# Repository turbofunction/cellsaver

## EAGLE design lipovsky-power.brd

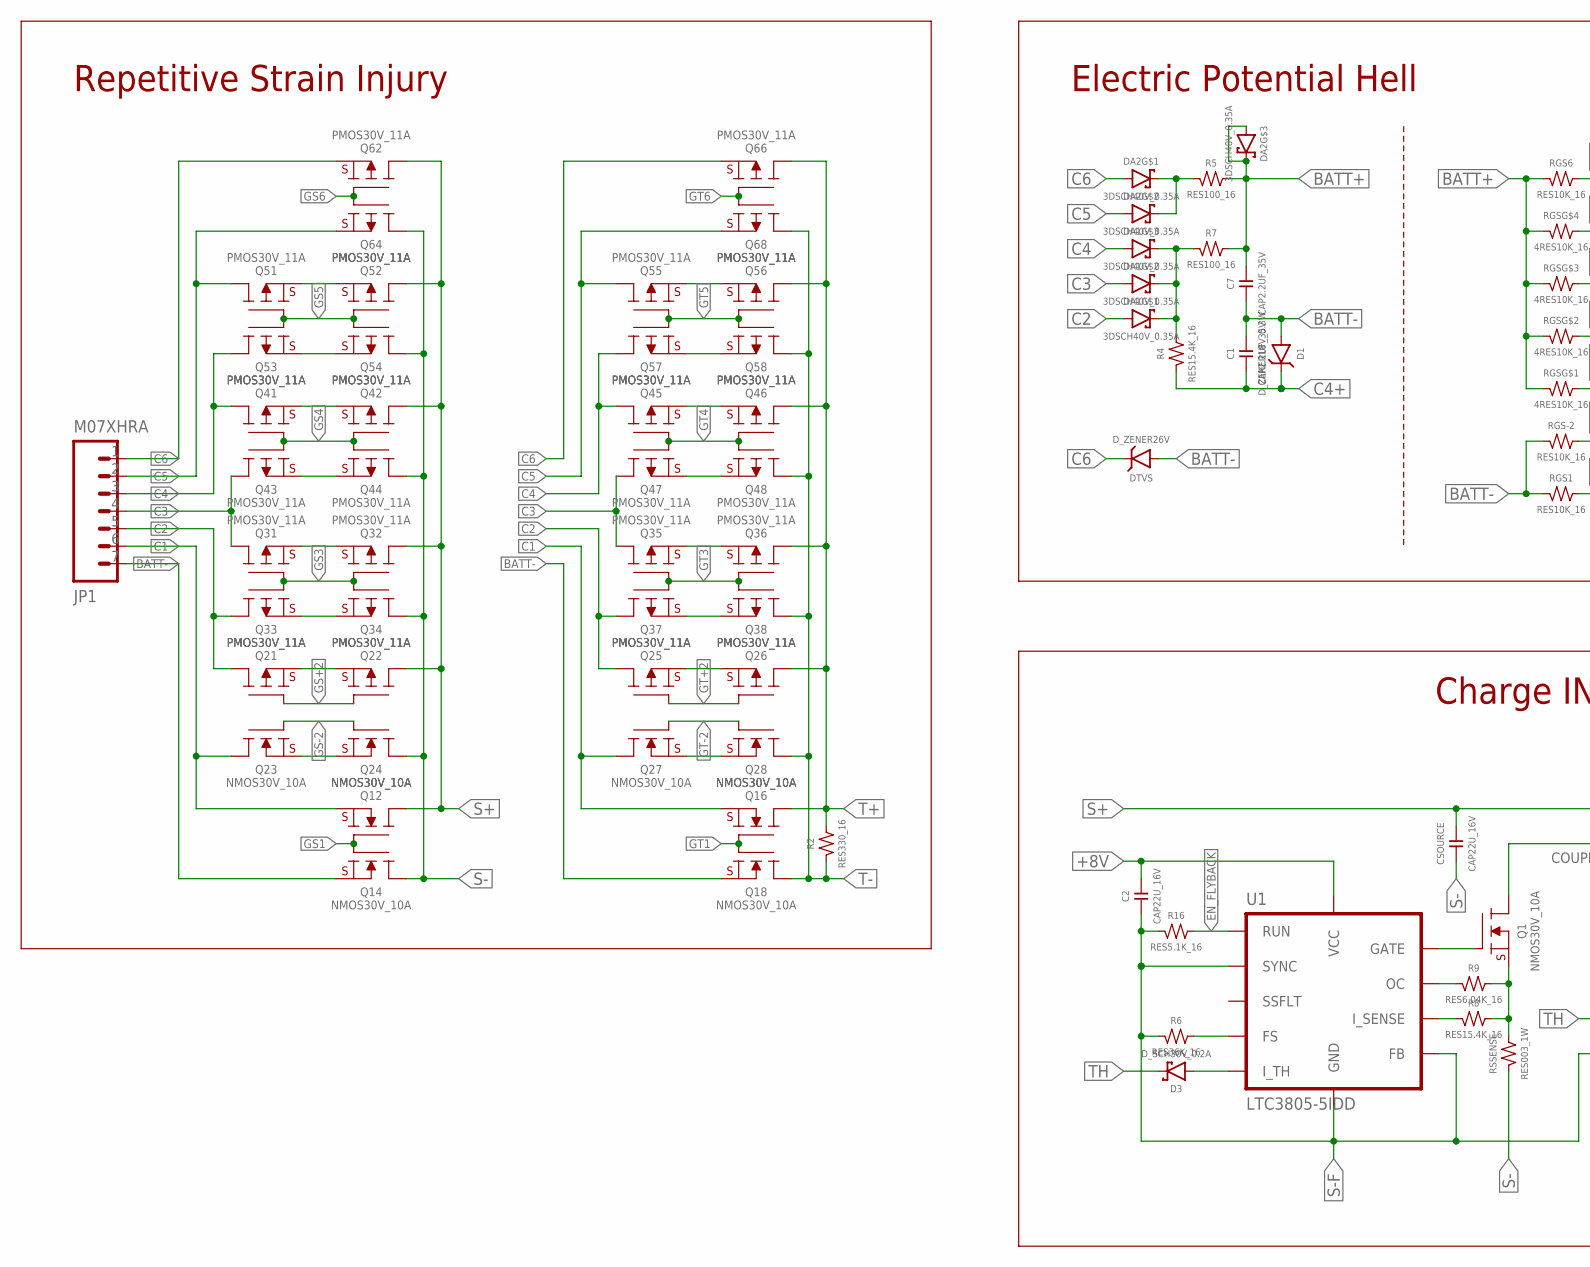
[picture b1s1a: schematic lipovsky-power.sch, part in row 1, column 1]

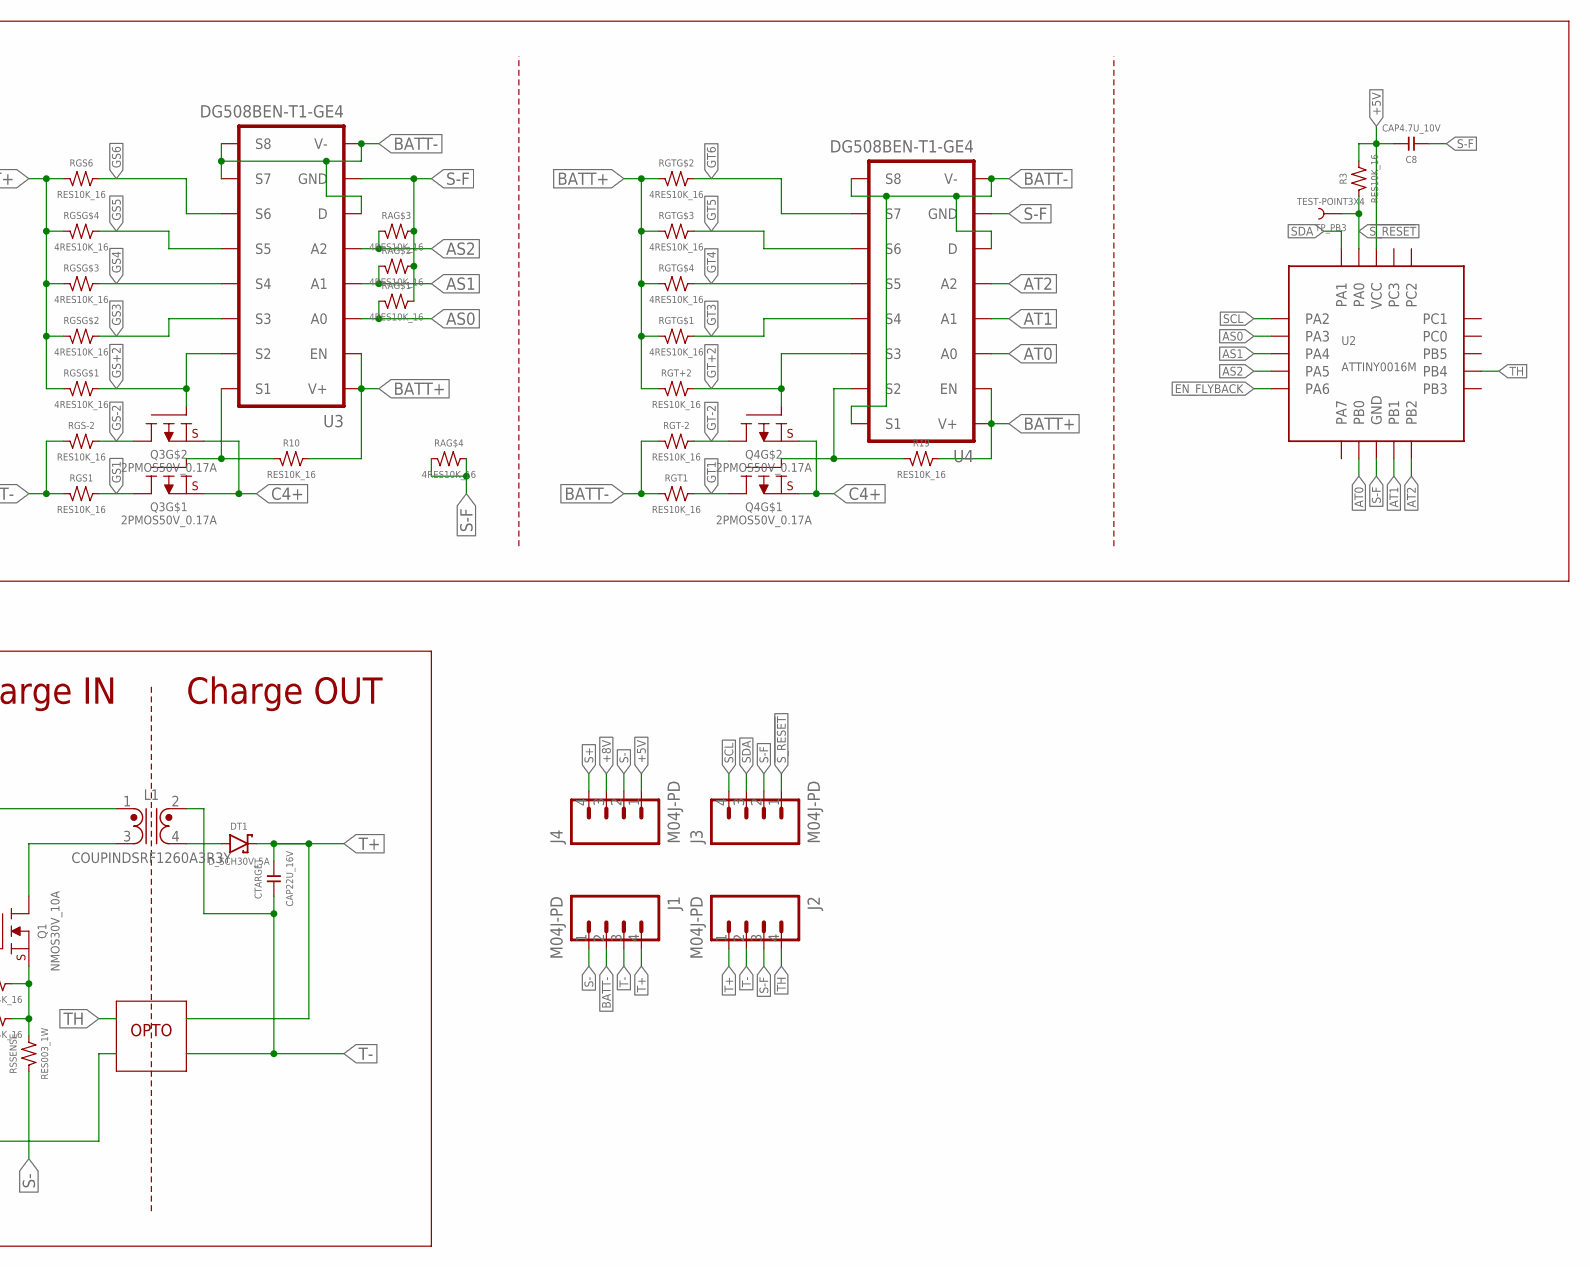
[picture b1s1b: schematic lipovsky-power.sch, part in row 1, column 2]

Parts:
C1, C7: CAP2.2UF_35V; 0402
C2: CAP22U_16V; 0805
C8: CAP4.7U_10V; 0603
CSOURCE: CAP22U_16V; 0805
CTARGET: CAP22U_16V; 0805
D1: D_ZENER18V_0.3W; SOD323+
D3: D_SCH30V_0.2A; SOD523+
DA1, DA2: 3DSCH40V_0.35A; SOT-363
DT1: D_SCH30V_5A; SOD-128
DTVS: D_ZENER26V; 2-UDFN
J1, J2, J3, J4: M04J-PD; 1X04_929J
JP1: M07XHRA; XH07-RA
L1: COUPINDSRF1260A3R3Y; SRF1260A
Q1, Q12, Q14, Q16, Q18, Q23, Q24, Q27, Q28: NMOS30V_10A; 6-POWERWDFN
Q3, Q4: 2PMOS50V_0.17A; SOT-666
Q21, Q22, Q25, Q26, Q31, Q32, Q33, Q34, Q35, Q36, Q37, Q38, Q41, Q42, Q43, Q44, Q45, Q46, Q47, Q48, Q51, Q52, Q53, Q54, Q55, Q56, Q57, Q58, Q62, Q64, Q66, Q68: PMOS30V_11A; 6-POWERWDFN
R2: RES330_16; 0402
R3, R10, R19: RES10K_16; 0402
R4, R8: RES15.4K_16; 0402
R5, R7: RES100_16; 0402
R6: RES36K_16; 0402
R9: RES6.04K_16; 0402
R16: RES5.1K_16; 0402
RA: 4RES10K_16; 1206-QUAD-LS
RGS: 4RES10K_16; 1206-QUAD-LS
RGS1, RGS6: RES10K_16; 0402
RGS-2: RES10K_16; 0402
RGT: 4RES10K_16; 1206-QUAD-LS
RGT1: RES10K_16; 0402
RGT+2: RES10K_16; 0402
RGT-2: RES10K_16; 0402
RSSENSE: RES003_1W; 1206
TP_PB3: TEST-POINT3X4; PAD.03X.04
U1: LTC3805-5IDD; 10-WFDFN
U2: ATTINY0016M; 20-VQFN-2
U3, U4: DG508BEN-T1-GE4; MINIQFN-16L

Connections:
!GS1: Q3.2 (G), R10.1, U3.2 (S1)
!GT1: Q4.2 (G), R19.1, U4.3 (S2)
!S_RESET: J3.1, R3.1, TP_PB3.P$1, U2.19 (PA0)
+5V: C8.2, J4.1, R3.2, U2.4 (VCC)
+8V: C2.2, J4.3, U1.7 (VCC)
AS0: RA.1, U2.2 (PA3), U3.15 (A0)
AS1: RA.2 (1), U2.5 (PA4), U3.14 (A1)
AS2: RA.3 (1), U2.6 (PA5), U3.13 (A2)
AT0: U2.14 (PB0), U4.15 (A0)
AT1: U2.13 (PB1), U4.14 (A1)
AT2: U2.12 (PB2), U4.13 (A2)
BATT+: C7.2, DA2.3 (C), DA2.4 (A), R5.2, R7.2, R10.2, R19.2, RGS.1, RGS.2 (1), RGS.3 (1), RGS.4 (1), RGS6.1, RGT.1, RGT.2 (1), RGT.3 (1), RGT.4 (1), RGT+2.1, U3.11 (V+), U3.16 (EN), U4.11 (V+), U4.16 (EN)
BATT-: C1.2, C7.1, D1.A, DTVS.A, J1.2, JP1.7, Q14.S, Q18.S, RGS1.1, RGS-2.1, RGT1.1, RGT-2.1, U3.1 (V-), U3.6 (D), U3.7 (S8), U3.8 (S7), U4.1 (V-), U4.2 (S1), U4.6 (D), U4.7 (S8)
C1: JP1.6, Q12.S, Q16.S, Q23.D, Q27.D
C2: DA1.6 (A), JP1.5, Q21.D, Q25.D, Q33.D, Q37.D
C3: DA1.5 (A), JP1.4, Q31.D, Q35.D, Q43.D, Q47.D
C4: DA1.4 (A), JP1.3, Q41.D, Q45.D, Q53.D, Q57.D
C4+: C1.1, D1.C, Q3.1 (S), Q3.4 (S), Q4.1 (S), Q4.4 (S), R4.1
C4D: DA1.1 (C), DA1.2 (C), DA1.3 (C), R4.2, R7.1
C5: DA2.5 (A), JP1.2, Q51.D, Q55.D, Q64.S, Q68.S
C6: DA2.6 (A), DTVS.C, JP1.1, Q62.S, Q66.S
C6D: DA2.1 (C), DA2.2 (C), R5.1
EN_FLYBACK: R16.2, U1.4 (RUN), U2.7 (PA6)
FS: R6.2, U1.5 (FS)
GATE: Q1.G, U1.6 (GATE)
GS1: Q3.6 (D), Q12.G, Q14.G, RGS1.2
GS3: Q31.G, Q32.G, Q33.G, Q34.G, RGS.7 (2), U3.4 (S3)
GS4: Q41.G, Q42.G, Q43.G, Q44.G, RGS.6 (2), U3.5 (S4)
GS5: Q51.G, Q52.G, Q53.G, Q54.G, RGS.5 (2), U3.10 (S5)
GS6: Q62.G, Q64.G, RGS6.2, U3.9 (S6)
GS+2: Q3.5 (G), Q21.G, Q22.G, RGS.8 (2), U3.3 (S2)
GS-2: Q3.3 (D), Q23.G, Q24.G, RGS-2.2
GT1: Q4.6 (D), Q16.G, Q18.G, RGT1.2
GT3: Q35.G, Q36.G, Q37.G, Q38.G, RGT.8 (2), U4.5 (S4)
GT4: Q45.G, Q46.G, Q47.G, Q48.G, RGT.5 (2), U4.10 (S5)
GT5: Q55.G, Q56.G, Q57.G, Q58.G, RGT.6 (2), U4.9 (S6)
GT6: Q66.G, Q68.G, RGT.7 (2), U4.8 (S7)
GT+2: Q4.5 (G), Q25.G, Q26.G, RGT+2.2, U4.4 (S3)
GT-2: Q4.3 (D), Q27.G, Q28.G, RGT-2.2
I_SENSE: R8.1, U1.9 (I_SENSE)
I_TH: D3.A, U1.2 (I_TH)
unnamed: DT1.A, L1.4 (B2)
unnamed: L1.3 (A2), Q1.D
OC: R9.1, U1.8 (OC)
S+: CSOURCE.2, J4.4, L1.1 (A1), Q12.D, Q22.D, Q32.D, Q42.D, Q52.D, Q62.D
S-: CSOURCE.1, J1.1, J4.2, Q14.D, Q24.D, Q34.D, Q44.D, Q54.D, Q64.D, RSSENSE.1
S-F: C2.1, C8.1, J2.3, J3.2, R6.1, R16.1, RA.4 (1), RA.5 (2), RA.6 (2), RA.7 (2), RA.8 (2), U1.3 (FB), U1.10 (SYNC), U1.PAD (GND), U2.3 (GND), U2.PAD (GND), U3.12 (GND), U4.12 (GND)
SCL: J3.4, U2.1 (PA2)
SDA: J3.3, U2.20 (PA1)
SENSE: Q1.S, R8.2, R9.2, RSSENSE.2
SS+2: Q21.S, Q22.S
SS+3: Q31.S, Q32.S
SS+4: Q41.S, Q42.S
SS+5: Q51.S, Q52.S
SS-2: Q23.S, Q24.S
SS-3: Q33.S, Q34.S
SS-4: Q43.S, Q44.S
SS-5: Q53.S, Q54.S
ST+2: Q25.S, Q26.S
ST+3: Q35.S, Q36.S
ST+4: Q45.S, Q46.S
ST+5: Q55.S, Q56.S
ST-2: Q27.S, Q28.S
ST-3: Q37.S, Q38.S
ST-4: Q47.S, Q48.S
ST-5: Q57.S, Q58.S
T+: CTARGET.2, DT1.C, J1.4, J2.1, Q16.D, Q26.D, Q36.D, Q46.D, Q56.D, Q66.D, R2.2
T-: CTARGET.1, J1.3, J2.2, L1.2 (B1), Q18.D, Q28.D, Q38.D, Q48.D, Q58.D, Q68.D, R2.1
TH: D3.C, J2.4, U2.10 (PB4)

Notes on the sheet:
Repetitive Strain Injury
Electric Potential Hell
Charge OUT
Charge IN
OPTO

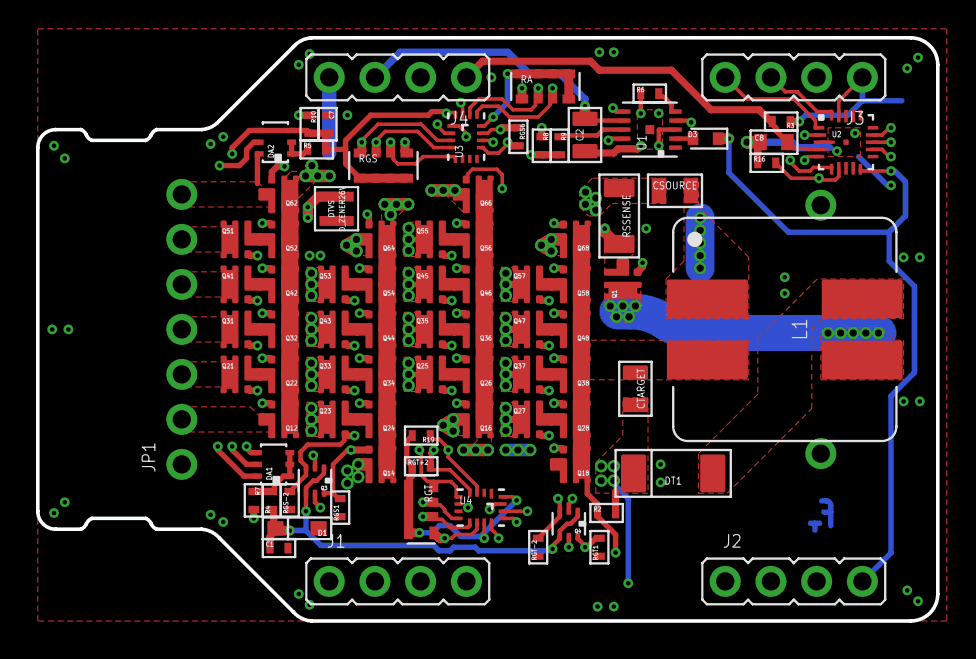
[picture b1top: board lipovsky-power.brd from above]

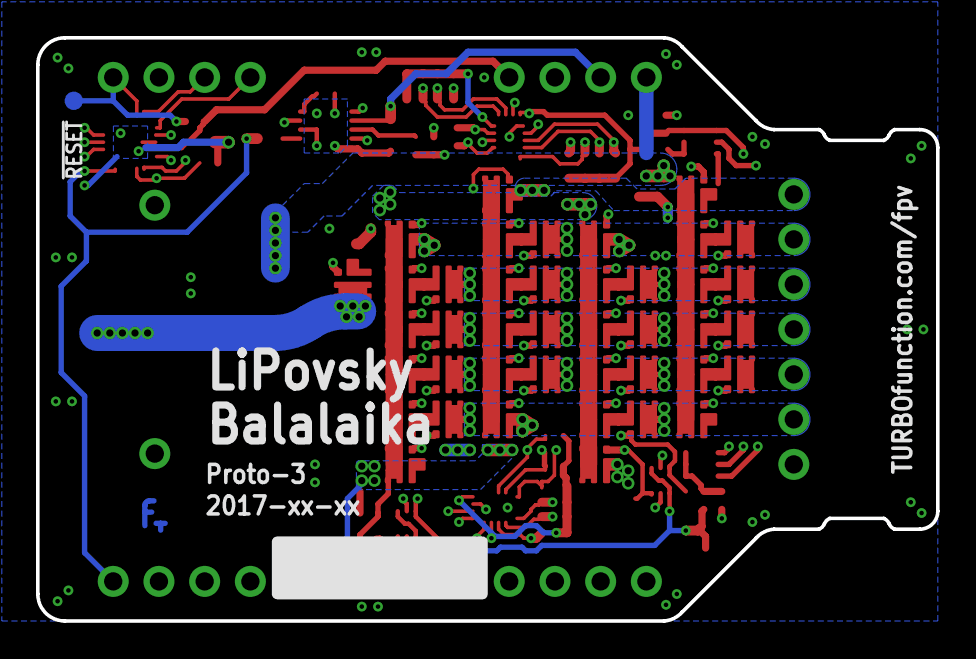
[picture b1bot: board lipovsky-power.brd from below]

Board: 4 copper layers, 50.0 x 32.4 mm, 88 parts (2 on the bottom side), 69 nets.

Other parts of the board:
ART1: TF-EMBLEM

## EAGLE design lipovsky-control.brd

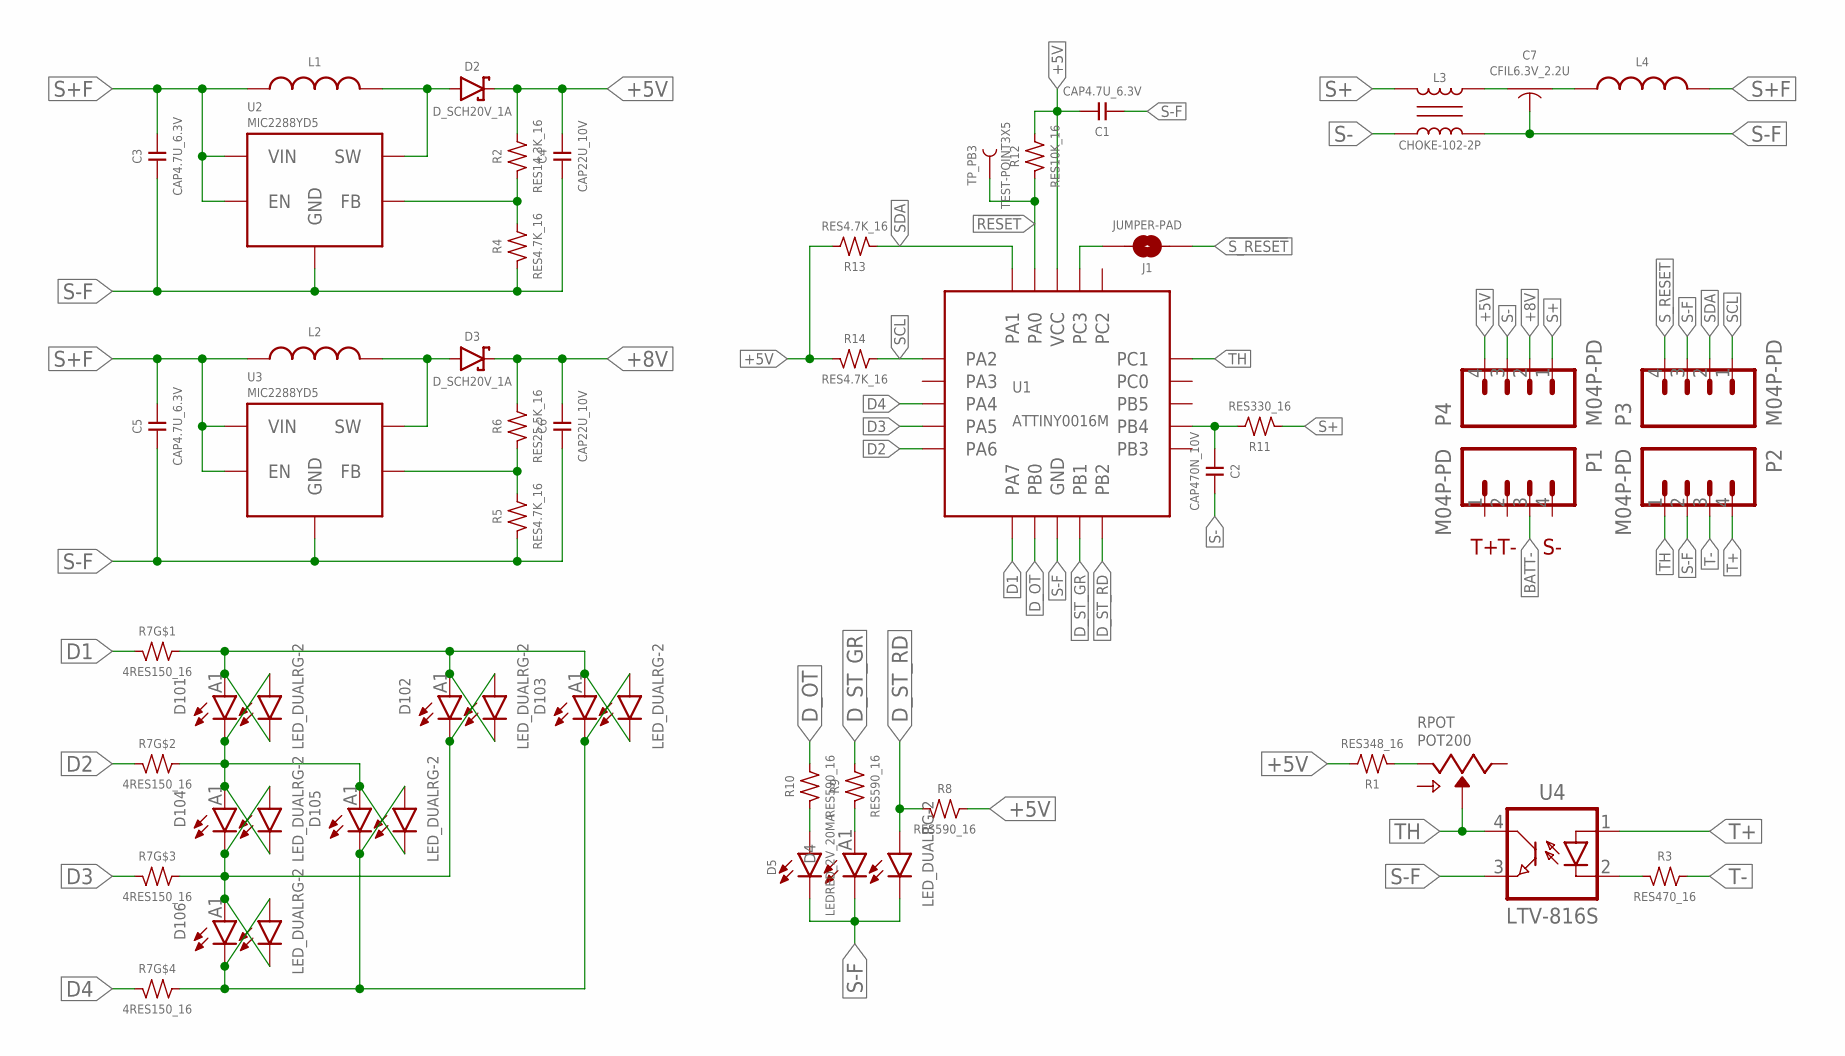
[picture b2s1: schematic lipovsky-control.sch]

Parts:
C1, C3, C5: CAP4.7U_6.3V; 0603
C2: CAP470N_10V; 0402
C4, C6: CAP22U_10V; 0603
C7: CFIL6.3V_2.2U; CFIL-0603
D2, D3: D_SCH20V_1A; SOD523+
D4, D101, D102, D103, D104, D105, D106: LED_DUALRG-2; 1206+DUAL
D5: LEDRED_2V_20MA; 1206+
J1: JUMPER-PAD; JUMPER-PAD-ROUND
L1: I4.7U_0.12A; 0603
L2: I10U_0.09A; 0603
L3: CHOKE-102-2P; APC3225
L4: I3.3UH_1A; 0603
P1, P2, P3, P4: M04P-PD; 1X04_929P
R1: RES348_16; 0402
R2: RES14.3K_16; 0402
R3: RES470_16; 0402
R4, R5, R13, R14: RES4.7K_16; 0402
R6: RES25.5K_16; 0402
R7: 4RES150_16; 1206-QUAD-LS
R8, R9, R10: RES590_16; 0402
R11: RES330_16; 0402
R12: RES10K_16; 0402
RPOT: POT200; TC33
TP_PB3: TEST-POINT3X5; PAD.03X.05
U1: ATTINY0016M; 20-VQFN-2
U2, U3: MIC2288YD5; SOT-23-5
U4: LTV-816S; 4-OPTO-1

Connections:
!RESET: R12.1, TP_PB3.P$1, U1.19 (PA0)
!S_RESET: J1.1, P3.4
+5V: C1.2, C4.2, D2.C, P4.4, R1.2, R2.2, R8.2, R12.2, R13.2, R14.1, U1.4 (VCC)
+8V: C6.2, D3.C, P4.2, R6.2
BATT-: P1.3
D1: R7.1, U1.8 (PA7)
D1L: D101.A1, D101.C2, D102.A1, D102.C2, D103.A1, D103.C2, R7.8 (2)
D2: R7.2 (1), U1.7 (PA6)
D2L: D101.A2, D101.C1, D104.A1, D104.C2, D105.A1, D105.C2, R7.7 (2)
D3: R7.3 (1), U1.6 (PA5)
D3L: D102.A2, D102.C1, D104.A2, D104.C1, D106.A1, D106.C2, R7.6 (2)
D4: R7.4 (1), U1.5 (PA4)
D4L: D103.A2, D103.C1, D105.A2, D105.C1, D106.A2, D106.C1, R7.5 (2)
D_OT: R10.2, U1.14 (PB0)
D_ST_GR: R9.2, U1.13 (PB1)
D_ST_RD: D4.A2, R8.1, U1.12 (PB2)
unnamed: R3.1, U4.2 (K)
unnamed: D5.A, R10.1
unnamed: J1.2, U1.18 (PC3)
unnamed: D2.A, L1.2, U2.1 (SW)
unnamed: D4.A1, R9.1
unnamed: C7.1, L3.P$4 (4)
unnamed: C7.2, L4.1
unnamed: R1.1, RPOT.CCW
unnamed: D3.A, L2.2, U3.1 (SW)
unnamed: R5.2, R6.1, U3.3 (FB)
unnamed: R2.1, R4.2, U2.3 (FB)
S+: L3.P$1 (1), P4.1, R11.1
S+F: C3.2, C5.2, L1.1, L2.1, L4.2, U2.4 (EN), U2.5 (VIN), U3.4 (EN), U3.5 (VIN)
S-: C2.2, L3.P$2 (2), P4.3
S-F: C1.1, C3.1, C4.1, C5.1, C6.1, C7.GND, D4.C1, D4.C2, D5.C, L3.P$3 (3), P2.2, P3.3, R4.1, R5.1, U1.3 (GND), U1.PAD (GND), U2.2 (GND), U3.2 (GND), U4.3 (E)
SCL: P3.1, R14.2, U1.1 (PA2)
SDA: P3.2, R13.1, U1.20 (PA1)
S_ADC: C2.1, R11.2, U1.10 (PB4)
T+: P2.4, U4.1 (A)
T-: P2.3, R3.2
TH: P2.1, RPOT.WIPER, U1.16 (PC1), U4.4 (C)

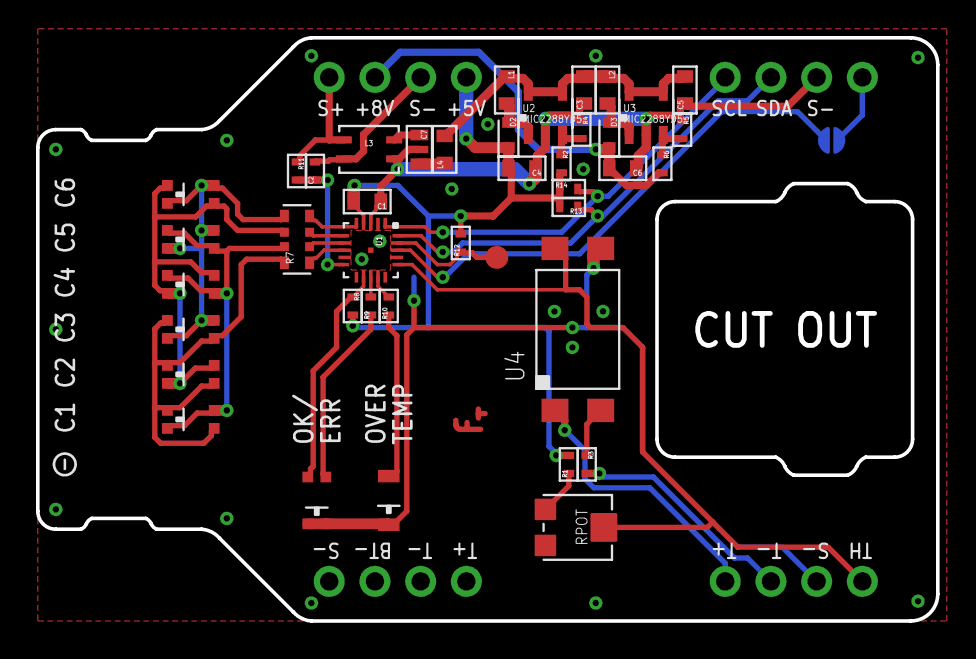
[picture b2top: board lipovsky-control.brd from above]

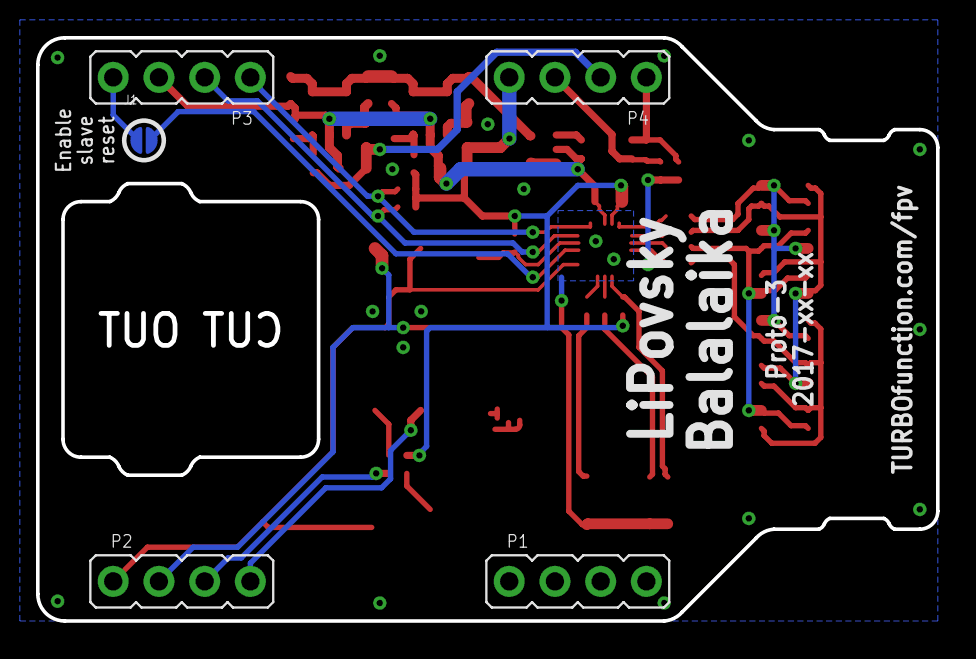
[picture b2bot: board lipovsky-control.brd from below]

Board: 2 copper layers, 50.0 x 32.4 mm, 47 parts (5 on the bottom side), 36 nets.

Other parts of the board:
U$1: TF-EMBLEM

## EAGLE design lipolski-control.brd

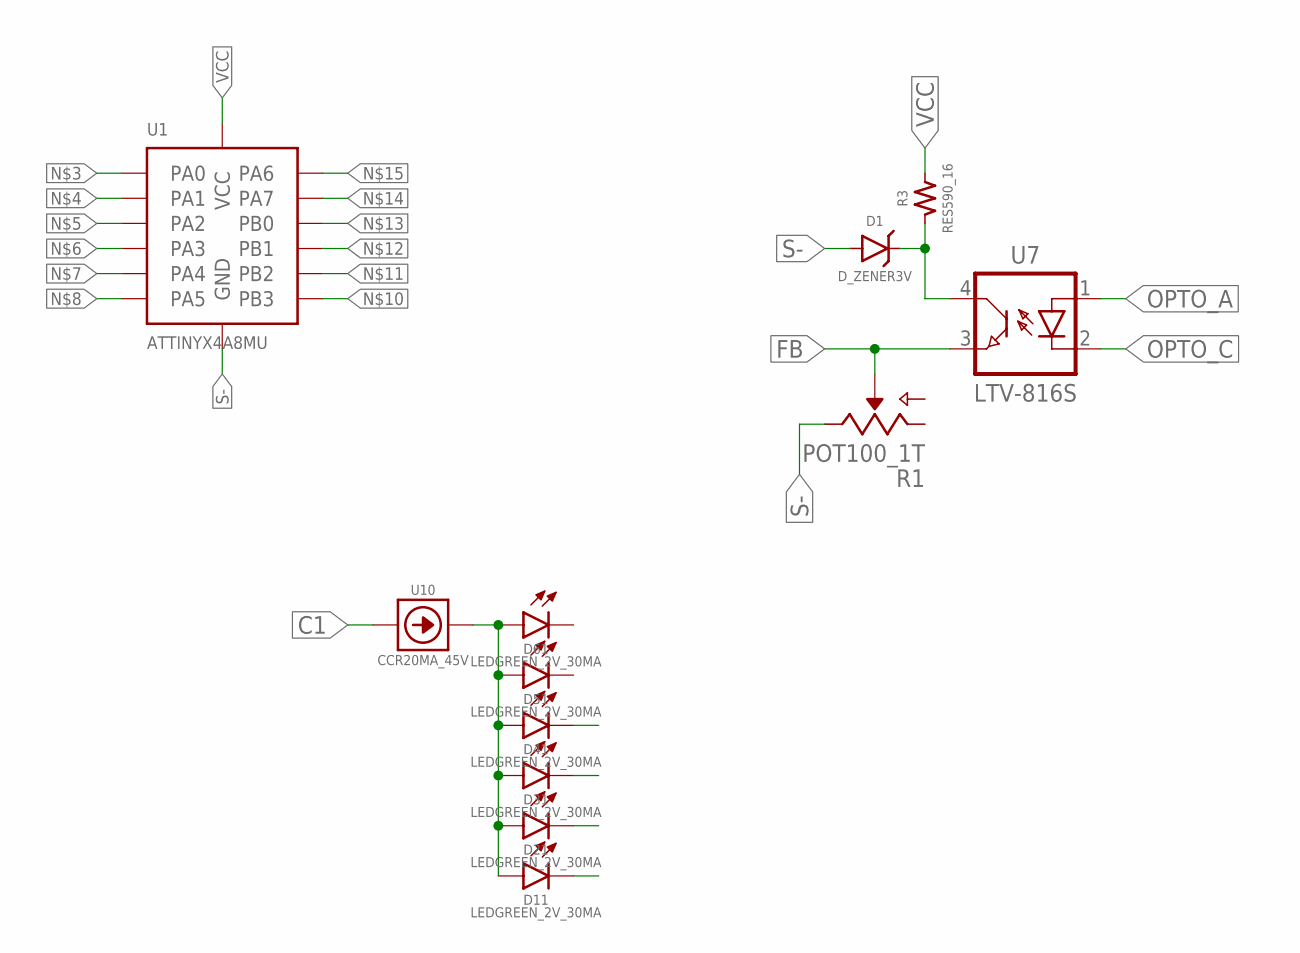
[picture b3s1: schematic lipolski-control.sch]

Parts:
D1: D_ZENER3V; SOT23-3
D11, D21, D31, D41, D51, D61: LEDGREEN_2V_30MA; 0603+
R1: POT100_1T; ST-4EA
R3: RES590_16; 0402
U1: ATTINYX4A8MU; ATTINYX4A
U7: LTV-816S; 4-OPTO-1
U10: CCR20MA_45V; SOD-123

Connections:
C1: U10.A
FB: R1.2 (S), U7.3 (E)
unnamed: D1.3 (C), R3.1, U7.4 (C)
unnamed: D11.A, D21.A, D31.A, D41.A, D51.A, D61.A, U10.C
OPTO_A: U7.1 (A)
OPTO_C: U7.2 (K)
S-: D1.1 (A), R1.3 (E), U1.8 (GND), U1.PAD (GND)
VCC: R3.2, U1.9 (VCC)

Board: 4 copper layers, 12 parts (0 on the bottom side), 5 nets, no tracks yet.

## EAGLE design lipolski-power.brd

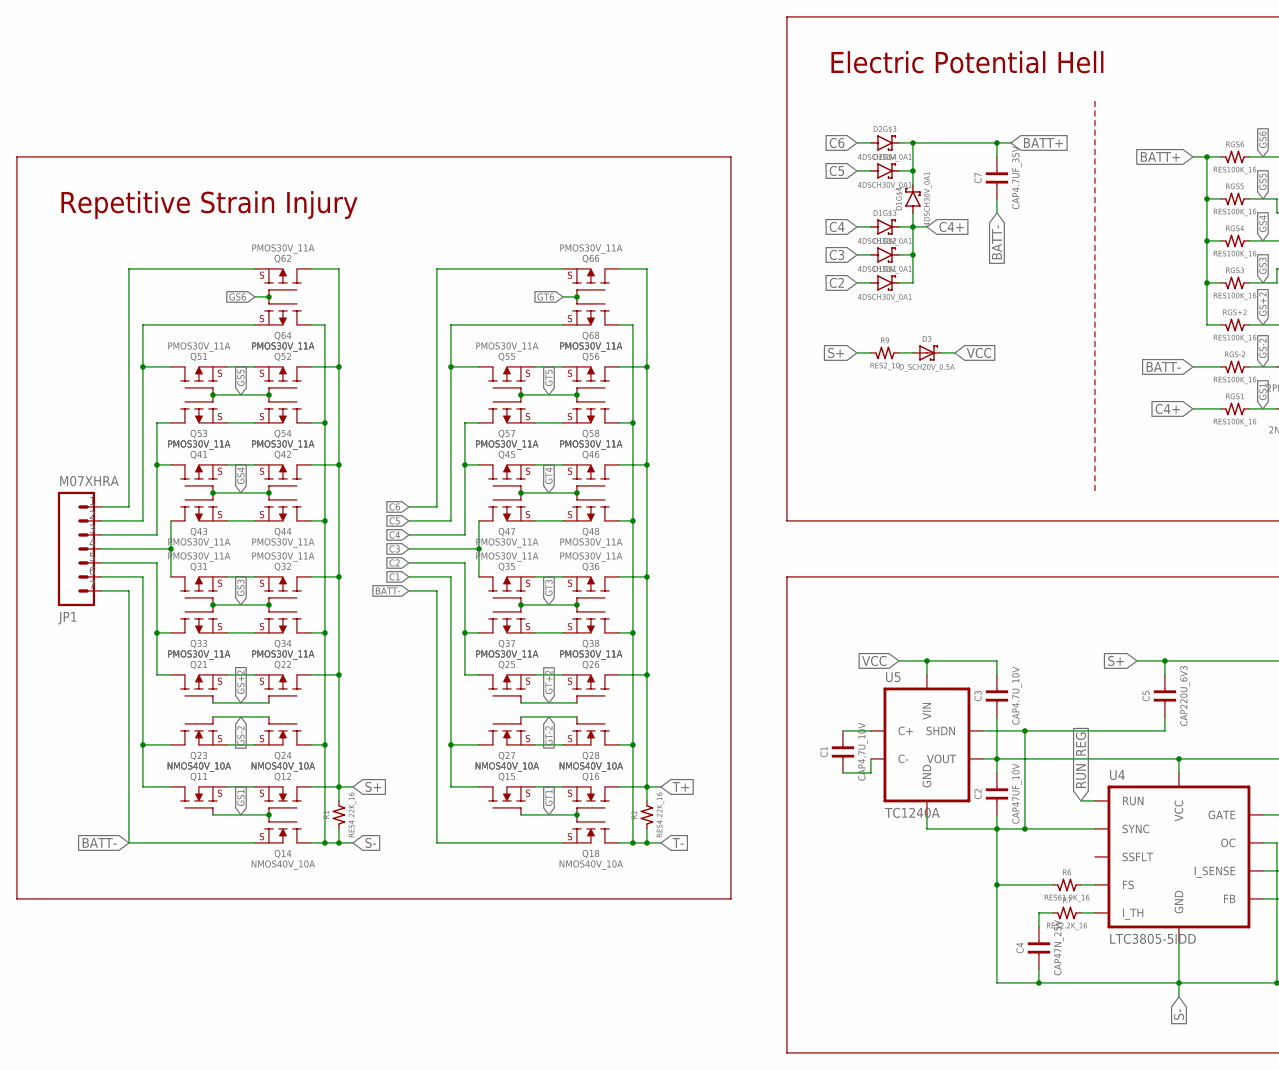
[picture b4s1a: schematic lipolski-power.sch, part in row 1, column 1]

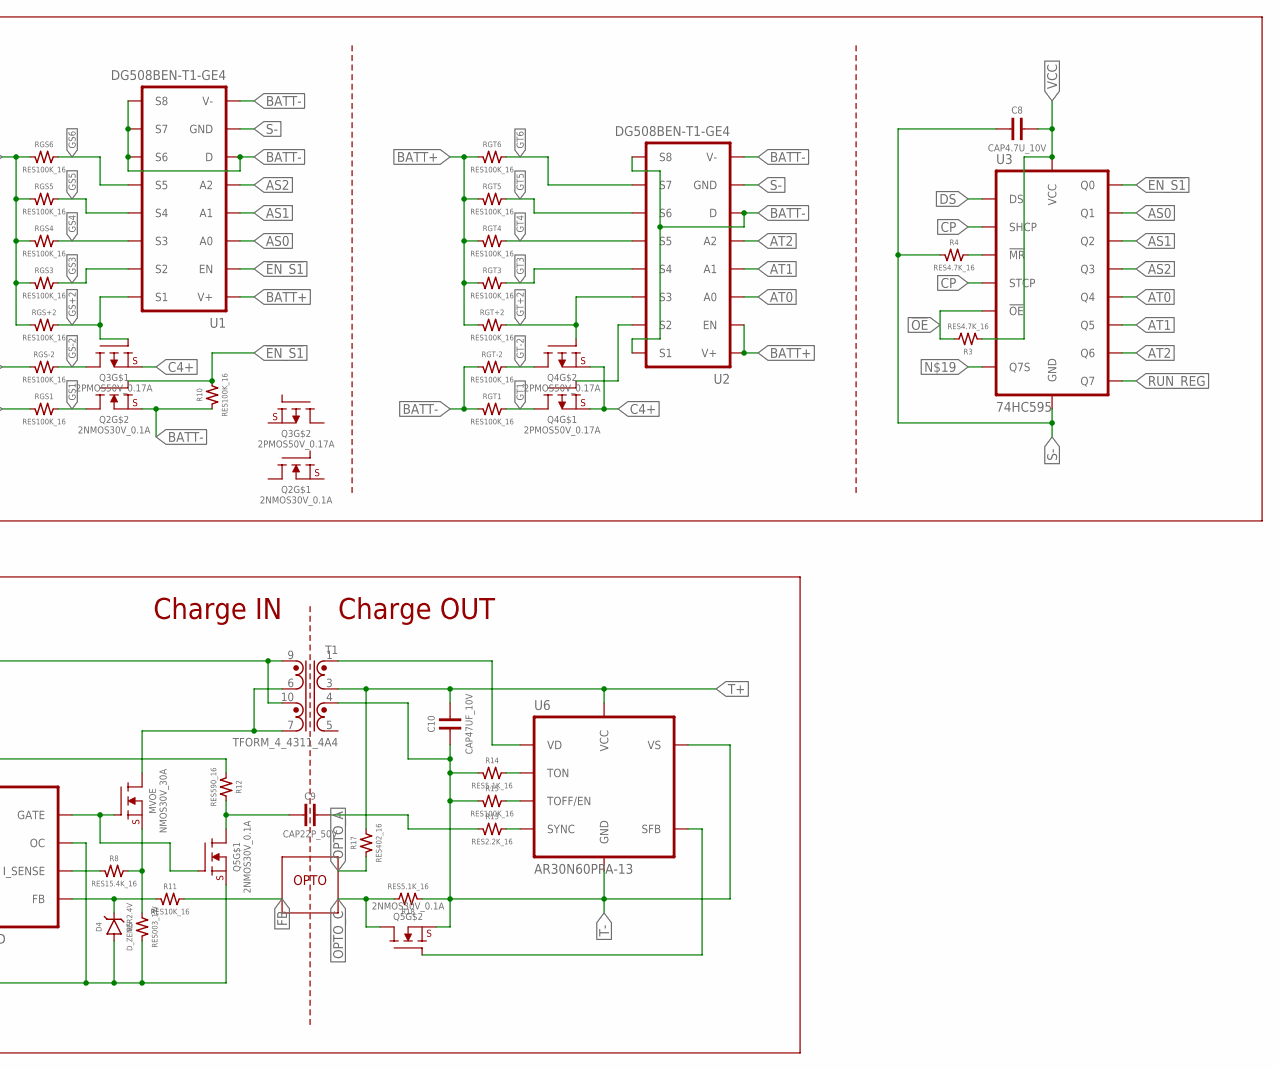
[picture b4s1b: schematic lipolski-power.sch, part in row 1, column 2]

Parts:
C1, C3, C8: CAP4.7U_10V; 0603
C2, C10: CAP47UF_10V; 0805
C4: CAP47N_25V; 0402
C5: CAP220U_6V3; 1210
C7: CAP4.7UF_35V; 0603
C9: CAP22P_50V; 0402
D1, D2: 4DSCH30V_0A1; 8-HMD
D3: D_SCH20V_0.5A; SOD523+
D4: D_ZENER2.4V; SOD523+
JP1: M07XHRA; XH07-RA
MVOE: NMOS30V_30A; 8-POWERWDFN
Q2, Q5: 2NMOS30V_0.1A; SOT-666
Q3, Q4: 2PMOS50V_0.17A; SOT-666
Q11, Q12, Q14, Q15, Q16, Q18, Q23, Q24, Q27, Q28: NMOS40V_10A; 6-POWERWDFN
Q21, Q22, Q25, Q26, Q31, Q32, Q33, Q34, Q35, Q36, Q37, Q38, Q41, Q42, Q43, Q44, Q45, Q46, Q47, Q48, Q51, Q52, Q53, Q54, Q55, Q56, Q57, Q58, Q62, Q64, Q66, Q68: PMOS30V_11A; 6-POWERWDFN
R1, R2: RES4.22K_16; 0402
R3, R4: RES4.7K_16; 0402
R5: RES003_1W; 1206
R6: RES61.9K_16; 0402
R7, R13: RES2.2K_16; 0402
R8: RES15.4K_16; 0402
R9: RES2_10; 0603
R10, R15: RES100K_16; 0402
R11: RES10K_16; 0402
R12: RES590_16; 0402
R14, R18: RES5.1K_16; 0402
R17: RES402_16; 0402
RGS1, RGS3, RGS4, RGS5, RGS6: RES100K_16; 0402
RGS+2: RES100K_16; 0402
RGS-2: RES100K_16; 0402
RGT1, RGT3, RGT4, RGT5, RGT6: RES100K_16; 0402
RGT+2: RES100K_16; 0402
RGT-2: RES100K_16; 0402
T1: TFORM_4_4311_4A4; EPQ13
U1, U2: DG508BEN-T1-GE4; MINIQFN-16L
U3: 74HC595; 16-VFQFN
U4: LTC3805-5IDD; 10-WFDFN
U5: TC1240A; SOT-23-6
U6: AR30N60PPA-13; 22-VFDFN

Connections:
!EN_S1: Q2.5 (G), R10.2, U1.16 (EN), U3.15 (Q0)
!OE: R3.2, U3.13 (!OE)
AS0: U1.15 (A0), U3.1 (Q1)
AS1: U1.14 (A1), U3.2 (Q2)
AS2: U1.13 (A2), U3.3 (Q3)
AT0: U2.15 (A0), U3.4 (Q4)
AT1: U2.14 (A1), U3.5 (Q5)
AT2: U2.13 (A2), U3.6 (Q6)
BATT+: C7.2, D1.5 (C), D2.5 (C), D2.6 (C), RGS3.1, RGS4.1, RGS5.1, RGS6.1, RGS+2.1, RGT3.1, RGT4.1, RGT5.1, RGT6.1, RGT+2.1, U1.11 (V+), U2.11 (V+), U2.16 (EN)
BATT-: C7.1, JP1.7, Q2.4 (S), Q14.S, Q18.S, R10.1, RGS-2.1, RGT1.1, RGT-2.1, U1.1 (V-), U1.6 (D), U1.7 (S8), U1.8 (S7), U1.9 (S6), U2.1 (V-), U2.2 (S1), U2.6 (D), U2.7 (S8)
C1: JP1.6, Q11.D, Q15.D, Q23.D, Q27.D
C2: D1.1 (A), JP1.5, Q21.D, Q25.D, Q33.D, Q37.D
C3: D1.2 (A), JP1.4, Q31.D, Q35.D, Q43.D, Q47.D
C4: D1.3 (A), JP1.3, Q41.D, Q45.D, Q53.D, Q57.D
C4+: D1.4 (A), D1.6 (C), D1.7 (C), D1.8 (C), Q3.1 (S), Q4.1 (S), Q4.4 (S), RGS1.1
C5: D2.4 (A), JP1.2, Q51.D, Q55.D, Q64.S, Q68.S
C6: D2.3 (A), JP1.1, Q62.S, Q66.S
CP: U3.11 (SHCP), U3.12 (STCP)
DS: U3.14 (DS)
FB: R11.2
GS1: Q2.3 (D), Q11.G, Q12.G, Q14.G, RGS1.2
GS3: Q31.G, Q32.G, Q33.G, Q34.G, RGS3.2, U1.3 (S2)
GS4: Q41.G, Q42.G, Q43.G, Q44.G, RGS4.2, U1.4 (S3)
GS5: Q51.G, Q52.G, Q53.G, Q54.G, RGS5.2, U1.5 (S4)
GS6: Q62.G, Q64.G, RGS6.2, U1.10 (S5)
GS+2: Q3.2 (G), Q21.G, Q22.G, RGS+2.2, U1.2 (S1)
GS-2: Q3.6 (D), Q23.G, Q24.G, RGS-2.2
GT1: Q4.6 (D), Q15.G, Q16.G, Q18.G, RGT1.2
GT3: Q35.G, Q36.G, Q37.G, Q38.G, RGT3.2, U2.5 (S4)
GT4: Q45.G, Q46.G, Q47.G, Q48.G, RGT4.2, U2.10 (S5)
GT5: Q55.G, Q56.G, Q57.G, Q58.G, RGT5.2, U2.9 (S6)
GT6: Q66.G, Q68.G, RGT6.2, U2.8 (S7)
GT+2: Q4.5 (G), Q25.G, Q26.G, RGT+2.2, U2.4 (S3)
GT-2: Q4.3 (D), Q27.G, Q28.G, RGT-2.2
unnamed: D4.C, R11.1, U4.3 (FB)
unnamed: R4.2, U3.10 (!MR)
unnamed: R6.2, U4.5 (FS)
unnamed: MVOE.G, Q5.2 (G), U4.6 (GATE)
unnamed: R8.1, U4.9 (I_SENSE)
unnamed: MVOE.S, R5.2, R8.2
unnamed: C1.2, U5.6 (C+)
unnamed: C1.1, U5.3 (C-)
unnamed: MVOE.D, T1.6 (7), T1.7 (5)
unnamed: D3.A, R9.2
unnamed: R7.2, U4.2 (I_TH)
unnamed: C4.2, R7.1
unnamed: C9.1, Q5.6 (D), R12.2
unnamed: C9.2, R13.1
unnamed: R13.2, U6.19 (SYNC)
unnamed: Q4.2 (G), U2.3 (S2)
unnamed: R14.2, U6.1 (TON)
unnamed: R15.2, U6.2 (TOFF/EN)
unnamed: T1.1, U6.12-17 (VD), U6.VD
unnamed: Q5.5 (G), U6.3 (SFB)
OPTO_A: R17.1
OPTO_C: Q5.3 (D), R18.2
RUN_REG: U3.7 (Q7), U4.4 (RUN)
S+: C5.2, Q12.D, Q22.D, Q32.D, Q42.D, Q52.D, Q62.D, R1.2, R9.1, T1.9 (8), T1.10 (6)
S-: C2.1, C4.1, C5.1, C8.1, D4.A, Q5.1 (S), Q14.D, Q24.D, Q34.D, Q44.D, Q54.D, Q64.D, R1.1, R4.1, R5.1, R6.1, U1.12 (GND), U2.12 (GND), U3.8 (GND), U3.PAD (GND), U4.8 (OC), U4.10 (SYNC), U4.PAD (GND), U5.2 (GND), U5.4 (SHDN)
SS+1: Q11.S, Q12.S
SS+2: Q21.S, Q22.S
SS+3: Q31.S, Q32.S
SS+4: Q41.S, Q42.S
SS+5: Q51.S, Q52.S
SS-2: Q23.S, Q24.S
SS-3: Q33.S, Q34.S
SS-4: Q43.S, Q44.S
SS-5: Q53.S, Q54.S
ST+1: Q15.S, Q16.S
ST+2: Q25.S, Q26.S
ST+3: Q35.S, Q36.S
ST+4: Q45.S, Q46.S
ST+5: Q55.S, Q56.S
ST-2: Q27.S, Q28.S
ST-3: Q37.S, Q38.S
ST-4: Q47.S, Q48.S
ST-5: Q57.S, Q58.S
T+: C10.2, Q16.D, Q26.D, Q36.D, Q46.D, Q56.D, Q66.D, R2.2, R17.2, T1.3 (2), U6.22 (VCC)
T-: C10.1, Q5.4 (S), Q18.D, Q28.D, Q38.D, Q48.D, Q58.D, Q68.D, R2.1, R14.1, R15.1, R18.1, T1.4 (3), U6.5 (VS), U6.6-11 (VS), U6.21 (GND), U6.GND
VCC: C3.2, C8.2, D3.C, R3.1, U3.16 (VCC), U5.1 (VIN)
VCC_REG: C2.2, C3.1, R12.1, U4.7 (VCC), U5.5 (VOUT)

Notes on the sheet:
Repetitive Strain Injury
Electric Potential Hell
Charge OUT
Charge IN
OPTO

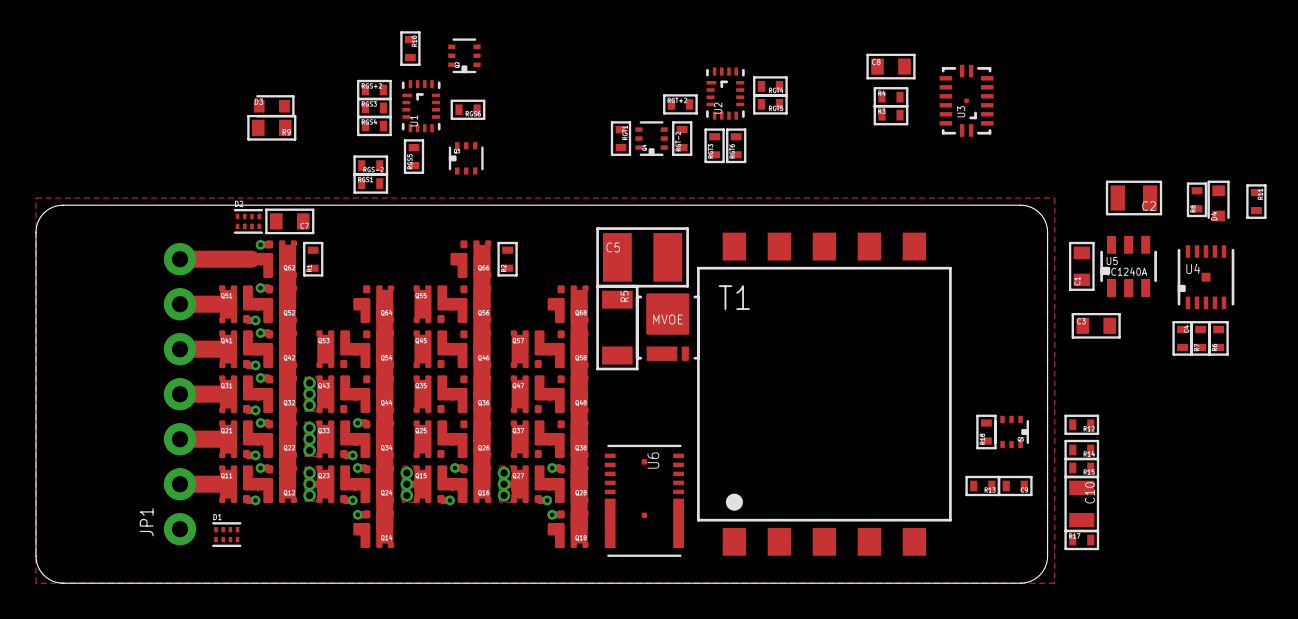
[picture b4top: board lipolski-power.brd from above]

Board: 4 copper layers, 56.2 x 21.0 mm, 99 parts (0 on the bottom side), 78 nets.

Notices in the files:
parts and their libraries:
SparkFun-Passives: Licensing: Creative Commons ShareAlike 4.0 International - https://creativecommons.org/licenses/by-sa/4.0
